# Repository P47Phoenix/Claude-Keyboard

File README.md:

# Claude Keyboard

A 25-key macropad companion for Claude Code terminal sessions — the **Claude Code Pad**. Dedicated hardware for firing CLI shortcuts (accept, reject, allow, arrow keys, commit/PR macros, plan/model cycle) with per-key RGB, a rotary encoder, a 2U stabilized Enter, and RFID artisan keycap support.

Wireless multi-host via BLE on a Seeed XIAO nRF52840; firmware runs [ZMK](https://zmk.dev).

## Status

**Design-complete (2026-04-23).** Gerbers + case STLs + firmware UF2 are produced, reviewed, and committed. Hardware bring-up + bench verification of the safety thresholds is the next physical step.

| Phase | Scope | State |
|---|---|---|
| 1 | PCB design (schematic, layout, routing, gerbers, BOM, CPL) | **Closed** (11 cycles) |
| 2 | 3D-printed case + bottom plate (CadQuery, PETG) | **Closed** (3 cycles) |
| 3 | Firmware (ZMK on nRF52840) | **Closed** (3 cycles) — `west build` clean, ztest 10/10 |
| 4 | TinyML callouts | **Retired** (Cycle 1 arbitration) |
| 5 | RFID figurine keycap base | **Retired** (post-Phase-3 scope decision) |
| 6 | Integration review | **Retired** (post-Phase-3 scope decision) |

PN532 NFC header + I²C bus remain on the PCB for any future revisit; firmware can wire them up later without a board respin.

## Hardware highlights

- **MCU:** Seeed XIAO nRF52840 (direct-solder castellations). BLE 5.x multi-host. Retired the initial XIAO ESP32-S3 + TinyML/OLED path in favour of a simpler, better-supported stack.
- **Keyswitches:** 24× 1U + 1× 2U Enter, Kailh MX hot-swap (Keebio `MX_Only_HS`), 19.05 mm pitch, Cherry plate-mount 2U stabilizer (slotted housing holes per community canonical footprint).
- **RGB:** 25× SK6812MINI-E reverse-mount, one per key, serpentine chain. Firmware-capped at 300 mA peak per IEC 62368-1 Annex Q.
- **Encoder:** EC11 with metal shaft grounded through plated mounting lugs; ESD TVS on all three encoder signals.
- **NFC:** PN532 header for RFID artisan figurine personality switching (Phase 5).
- **Power:** 1S LiPo via JST-PH with **mandatory cell-level protection PCB** (approved cells from Adafruit/SparkFun — see `docs/build-guide.md`). On-board DMG3415U-7 P-FET reverse-polarity, 500 mA PTC, SPDT slide switch. Charging via the XIAO's USB-C + on-module charger.
- **Safety:** NTC cell-temperature monitor, 5× ESD9L3.3 TVS on exposed I²C + encoder, firmware LED cap + VBAT undervoltage cutoff (3.70 V LEDs-on / 3.50 V LEDs-off).
- **Board:** 120 × 132 mm, 2-layer FR4, HASL lead-free, black soldermask. Freerouting-autorouted (1095 segments, 148 GND stitching vias, antenna keepout inviolate).

## Repository layout

```
claude-code-pad/
├── pcb/                           # Phase 1 deliverables
│   ├── claude-code-pad.kicad_pro|sch|pcb
│   ├── gerbers/                   # 10 layers + drill + job file (fab-ready)
│   ├── bom.csv / cpl.csv          # JLCPCB format
│   ├── DESIGN-NOTES.md            # design rationale + cycle history + pinout verification
│   └── _gen/                      # generator + autoroute pipeline
│       ├── generate.py            # schematic + placement source of truth
│       └── autoroute/             # export_dsn + freerouting + import_ses + widen_power + stitch_gnd
├── firmware/
│   ├── zmk/                       # Phase 3 primary (nRF52840 + ZMK)
│   │   └── README.md              # Hard Requirements for FW-1
│   └── qmk/                       # alternate path (RP2040)
├── case/                          # Phase 2 (MECH-1, CadQuery)
├── figurines/                     # Phase 5 (RFID artisan keycap)
└── docs/
    ├── build-guide.md             # MANDATORY battery requirements + assembly
    └── review-log.md              # Adversarial review paper trail
```

## Orchestration

Design work is done by **persona sub-agents** dispatched via Claude's Agent tool, not by the main thread:

- **Designers** (ECE-1 for PCB, MECH-1 for case, FW-1 for firmware) produce deliverables.
- **Adversarial reviewers** (RED-DFM, RED-SAFETY, RED-COST, RED-MECH, RED-FW) critique in parallel.
- Primary designer iterates until BLOCKER/MAJOR findings clear.
- Every cycle is logged in `claude-code-pad/docs/review-log.md`.

Full orchestration spec: `/var/home/meconnelly/Downloads/claude-code-pad-orchestrated-prompt.md` (authoritative for personas, phases, and reviewers).

## Tooling

This repo targets a **Bazzite** (immutable Fedora atomic) workstation. Package management notes and KiCad / Freerouting / Distrobox conventions are in [`CLAUDE.md`](./CLAUDE.md).

- **KiCad 10.0.1** as a Flatpak (`org.kicad.KiCad`) for GUI + authoritative file reads.
- **KiCad 9.0.8** in a `kicad` distrobox (Podman-backed Fedora 43 toolbox) for kicad-cli automation + the KiCad MCP server (`lamaalrajih/kicad-mcp`, auto-loaded via `.mcp.json`).
- **Freerouting 2.1.0** (Java 21) in the same distrobox for headless autorouting.
- **CadQuery / OpenSCAD** (Phase 2) — user-space Python, no Bazzite layering needed.

### Quick commands

```bash
# DRC via kicad-cli (flatpak, matches GUI rule set)
flatpak run --command=kicad-cli org.kicad.KiCad pcb drc \
  --output /tmp/drc.rpt pcb/claude-code-pad.kicad_pcb

# Open the PCB in the GUI
flatpak run --command=pcbnew org.kicad.KiCad pcb/claude-code-pad.kicad_pcb

# Re-run Freerouting (from distrobox)
distrobox enter kicad -- python3 pcb/_gen/autoroute/export_dsn.py pcb/claude-code-pad.kicad_pcb
distrobox enter kicad -- java -jar ~/.local/share/freerouting/freerouting.jar \
  -de /tmp/claude-code-pad.dsn -do /tmp/claude-code-pad.ses
distrobox enter kicad -- python3 pcb/_gen/autoroute/import_ses.py pcb/claude-code-pad.kicad_pcb
```

## Getting involved

If you want to build one:

1. Read [`claude-code-pad/docs/build-guide.md`](claude-code-pad/docs/build-guide.md) first — especially the **mandatory battery requirements** section.
2. Order the PCB from JLCPCB using `claude-code-pad/pcb/gerbers/` and `claude-code-pad/pcb/cpl.csv`.
3. Source the cells from the approved vendor list in the build guide. **Do not substitute a raw LiPo** — the board relies on cell-level protection PCM.
4. Wait for Phase 2 (case STL) and Phase 3 (ZMK firmware) before assembling a complete unit.

## License

TBD.

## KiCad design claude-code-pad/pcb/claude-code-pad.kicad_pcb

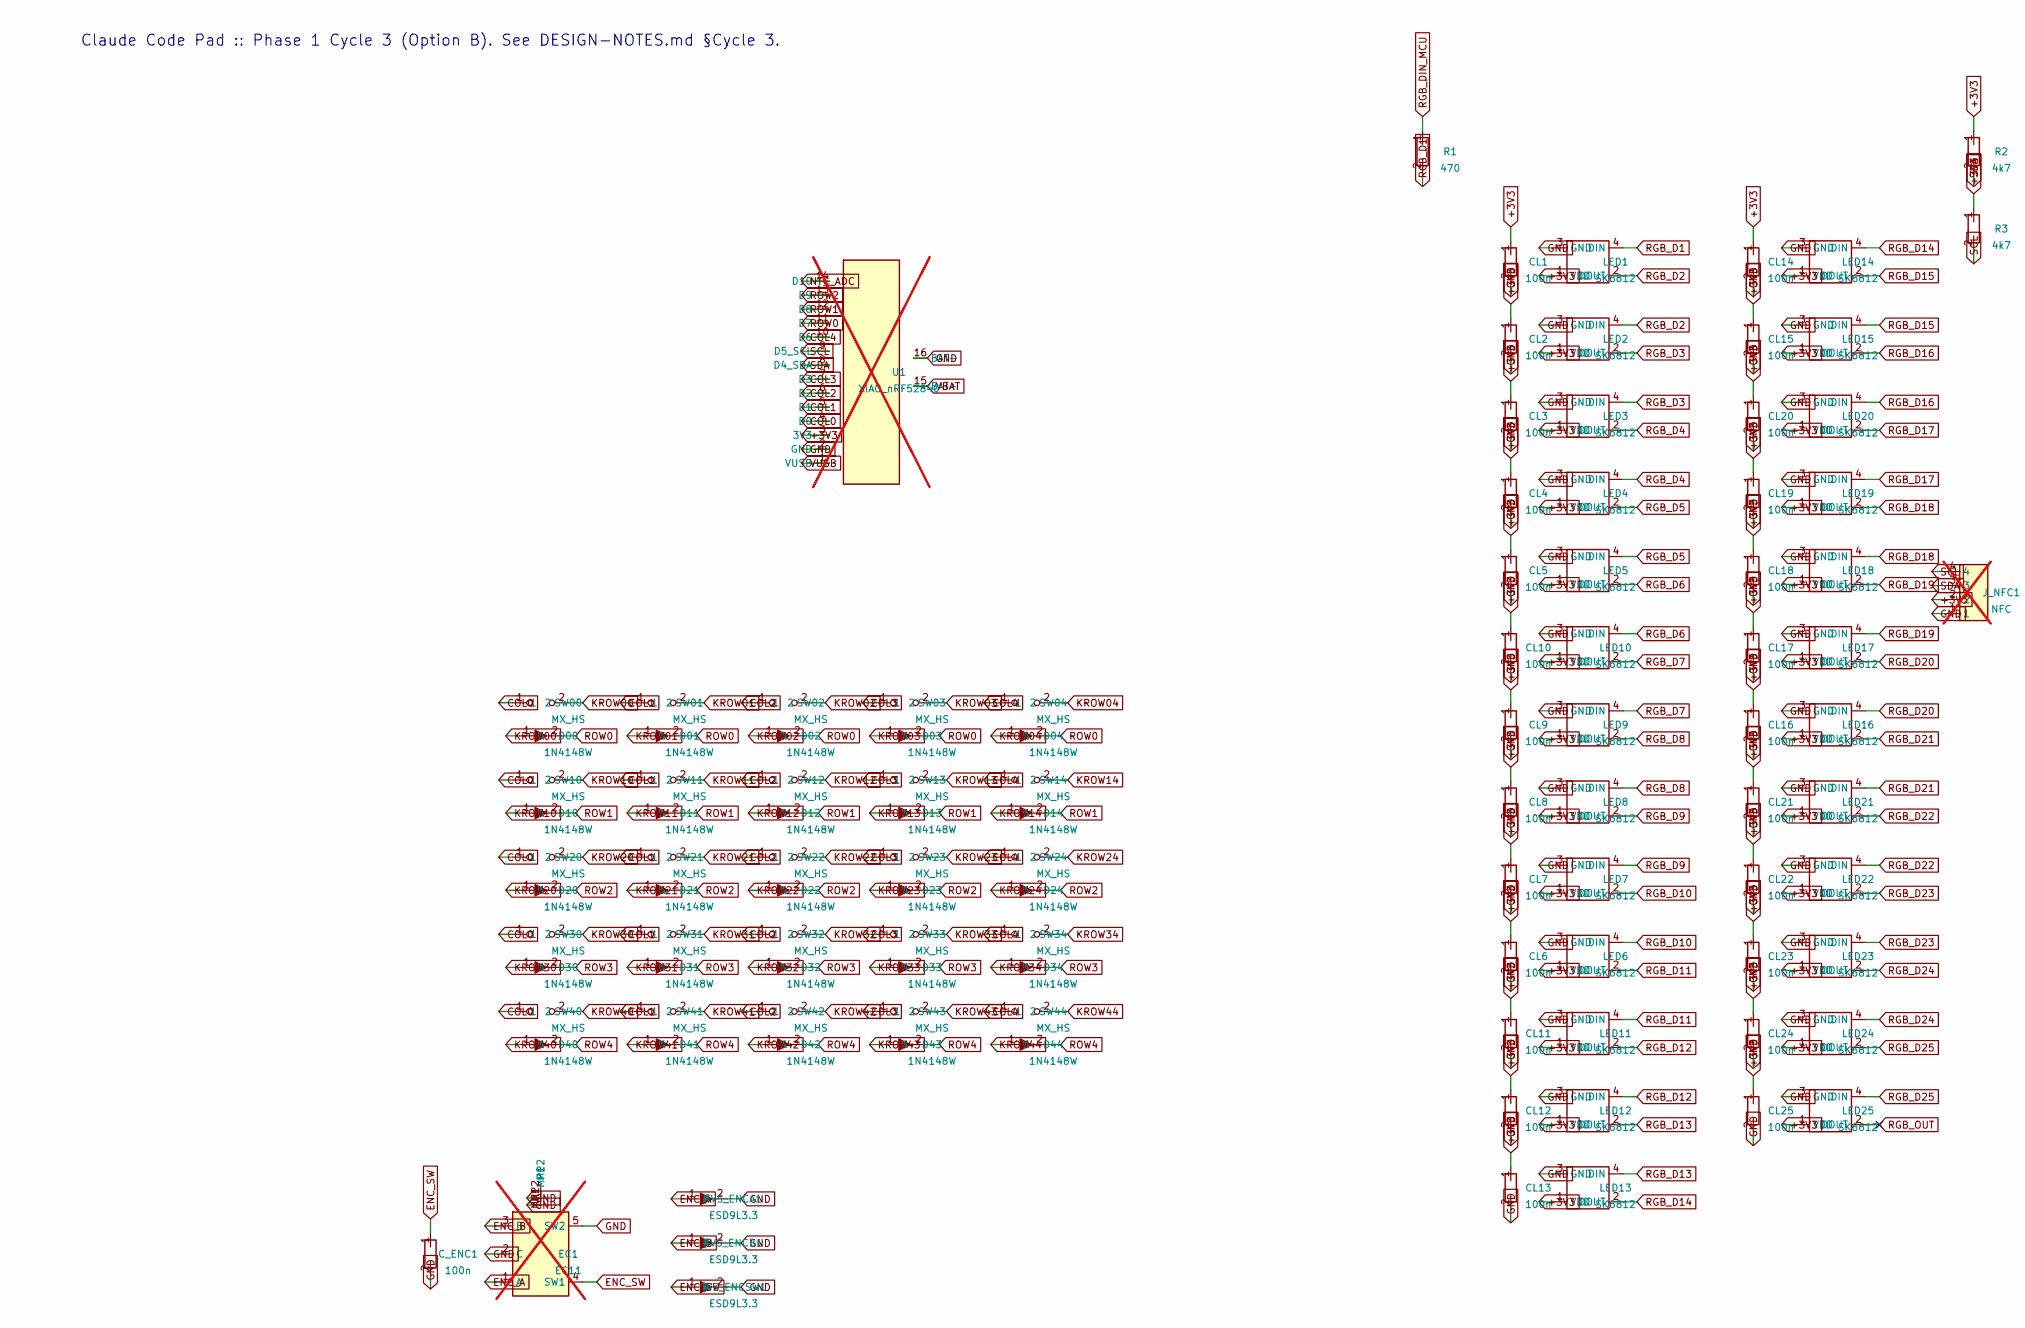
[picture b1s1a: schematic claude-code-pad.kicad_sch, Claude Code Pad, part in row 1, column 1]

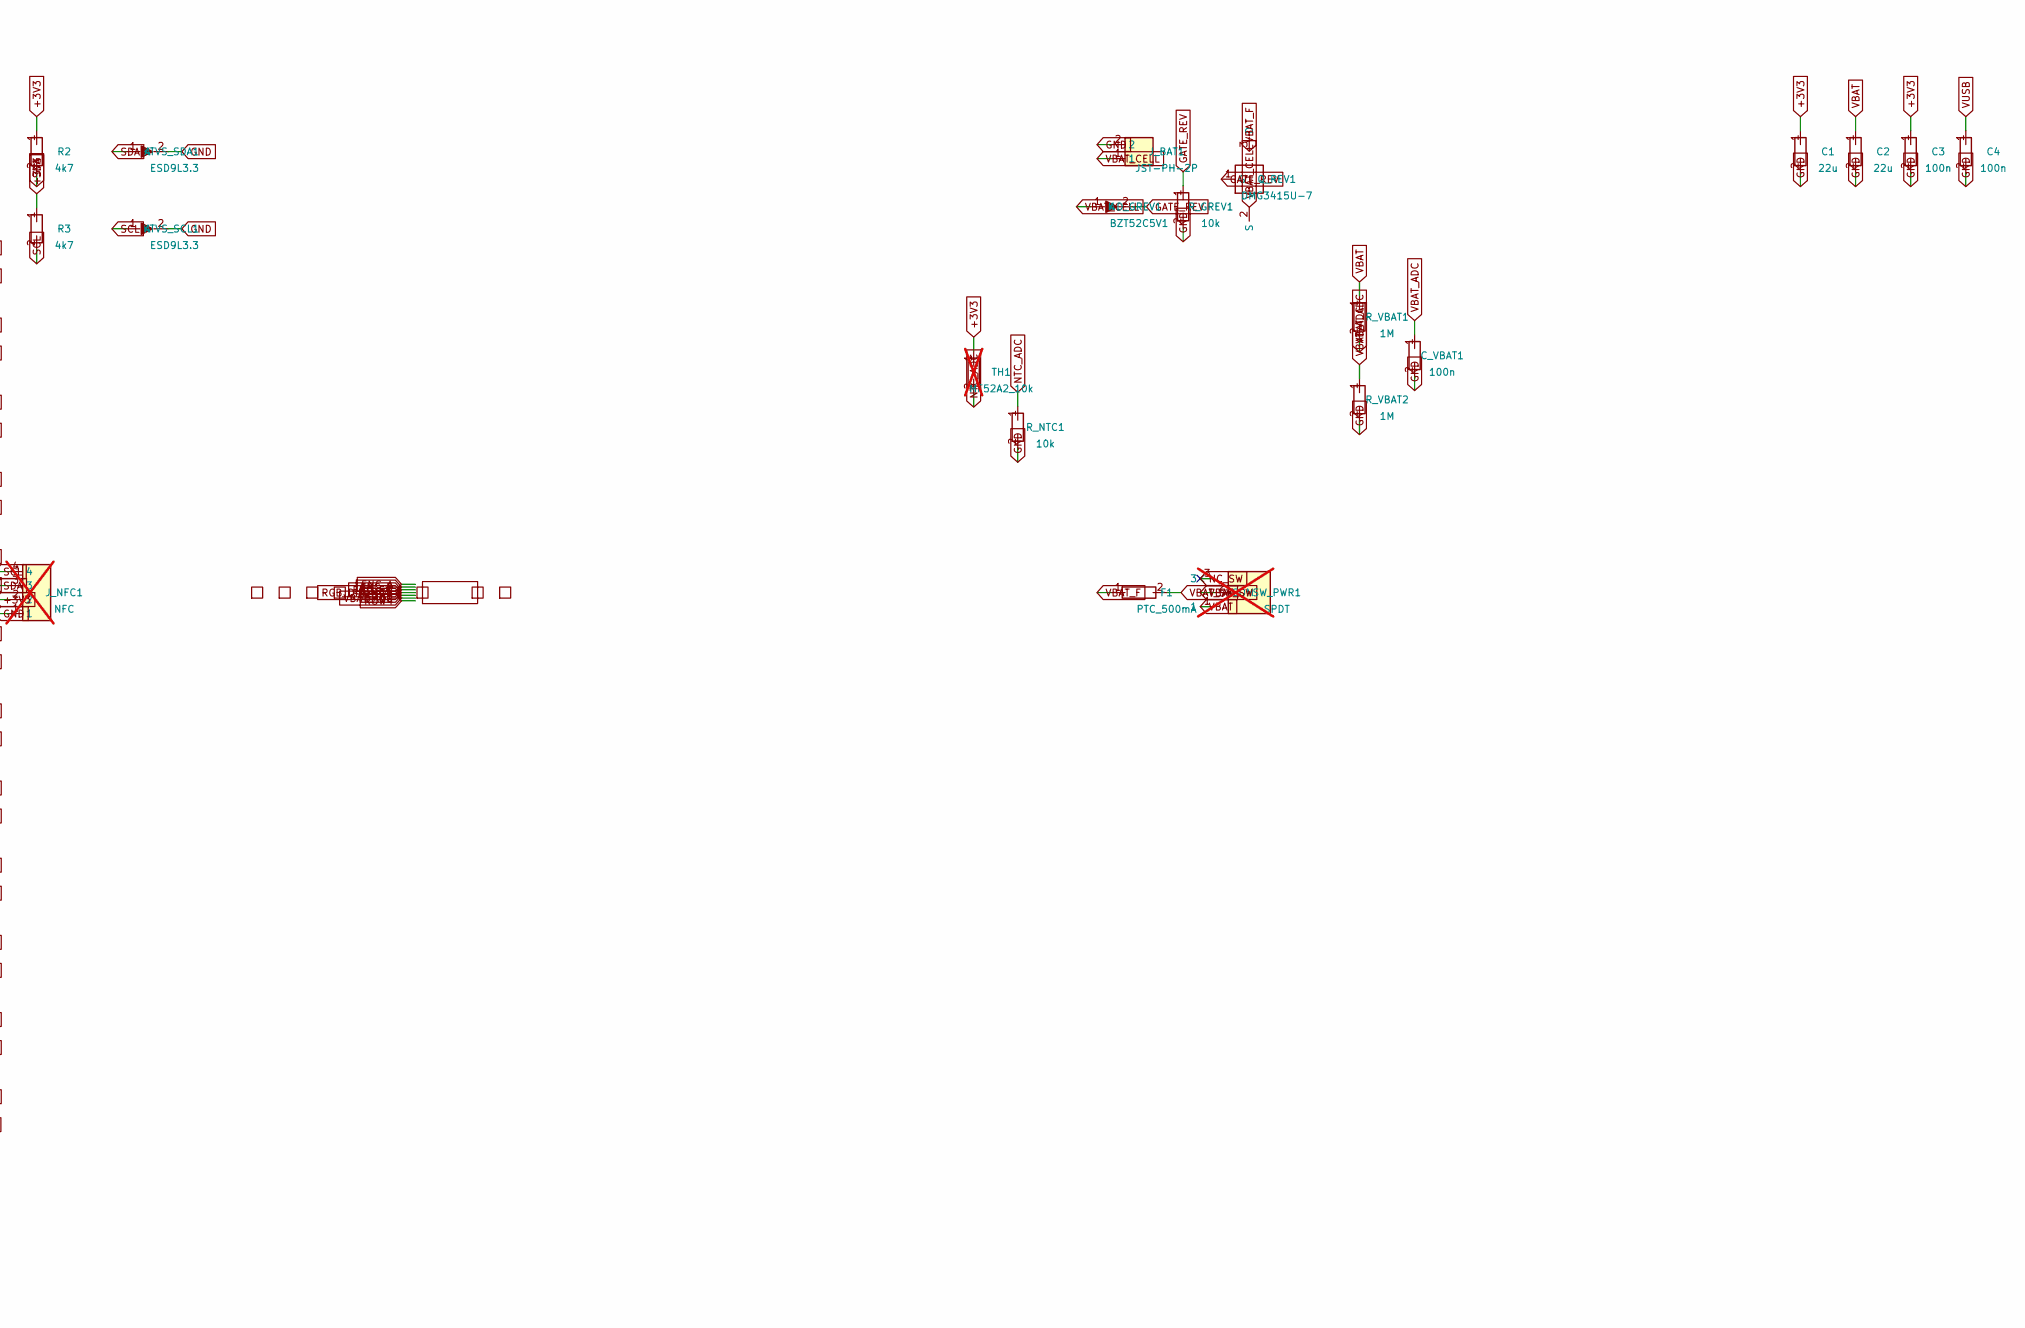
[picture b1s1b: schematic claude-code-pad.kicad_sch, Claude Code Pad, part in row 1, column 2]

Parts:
C1, C2: 22u; C_0805_2012Metric; LCSC C45783
C3, C4: 100n; C_0402_1005Metric; LCSC C1525
CL1, CL2, CL3, CL4, CL5, CL6, CL7, CL8, CL9, CL10, CL11, CL12, CL13, CL14, CL15, CL16, CL17, CL18, CL19, CL20, CL21, CL22, CL23, CL24, CL25: 100n; C_0402_1005Metric; LCSC C1525
C_ENC1: 100n; C_0402_1005Metric; LCSC C1525
C_VBAT1: 100n; C_0402_1005Metric; LCSC C1525
D00, D01, D02, D03, D04, D10, D11, D12, D13, D14, D20, D21, D22, D23, D24, D30, D31, D32, D33, D34, D40, D41, D42, D43, D44: 1N4148W; D_SOD-123; LCSC C81598
D_GREV1: BZT52C5V1; D_SOD-523; LCSC C8056
EC1: EC11; RotaryEncoder_Alps_EC11E-Switch_Vertical_H20mm; LCSC C255515; not fitted
F1: PTC_500mA; Fuse_0805_2012Metric; LCSC C116170
FID1, FID2, FID3: FID; Fiducial_1mm_Mask2mm
H1, H2: M3; MountingHole_3.2mm_M3
H3, H4: M3; MountingHole_3.2mm_M3_NPTH
J_BAT1: JST-PH-2P; JST_PH_S2B-PH-SM4-TB_1x02-1MP_P2.00mm_Horizontal; LCSC C295747
J_NFC1: NFC; PinHeader_1x04_P2.54mm_Vertical; not fitted
J_XIAO_BP: JUMPER; XIAO_BackPad_Jumper_1x7
LED1, LED2, LED3, LED4, LED5, LED6, LED7, LED8, LED9, LED10, LED11, LED12, LED13, LED14, LED15, LED16, LED17, LED18, LED19, LED20, LED21, LED22, LED23, LED24, LED25: SK6812; LED_SK6812_MINI-E_plccn4_3.5x2.8mm; LCSC C5149201
Q_REV1: DMG3415U-7; SOT-23; LCSC C147581
R1: 470; R_0402_1005Metric; LCSC C25744
R2, R3: 4k7; R_0402_1005Metric; LCSC C25905
R_GREV1: 10k; R_0402_1005Metric; LCSC C25804
R_NTC1: 10k; R_0402_1005Metric; LCSC C25804
R_VBAT1, R_VBAT2: 1M; R_0402_1005Metric; LCSC C22935
SW00, SW01, SW02, SW03, SW04, SW10, SW11, SW12, SW13, SW14, SW20, SW21, SW22, SW23, SW24, SW30, SW31, SW32, SW33, SW34, SW40, SW41, SW42, SW43: MX_HS; SW_Kailh_HotSwap_MX; LCSC C5184526
SW44: MX_HS; SW_Kailh_HotSwap_MX_2U; LCSC C5184526
SW_PWR1: SPDT; SW_Slide_1P2T_SS12D00G4; LCSC C8325; not fitted
TH1: MF52A2_10k; R_Axial_DIN0207_L6.3mm_D2.5mm_P7.62mm_Horizontal; LCSC C14128; not fitted
TP1, TP2: TOOL; MountingHole_1.5mm
TVS_ENCA1: ESD9L3.3; D_SOD-523; LCSC C709011
TVS_ENCB1: ESD9L3.3; D_SOD-523; LCSC C709011
TVS_ENCSW1: ESD9L3.3; D_SOD-523; LCSC C709011
TVS_SCL1: ESD9L3.3; D_SOD-523; LCSC C709011
TVS_SDA1: ESD9L3.3; D_SOD-523; LCSC C709011
U1: XIAO_nRF52840; XIAO_nRF52840_Castellated; LCSC C2888140; not fitted

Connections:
+3V3: C1.1, C3.1, CL1.1, CL2.1, CL3.1, CL4.1, CL5.1, CL6.1, CL7.1, CL8.1, CL9.1, CL10.1, CL11.1, CL12.1, CL13.1, CL14.1, CL15.1, CL16.1, CL17.1, CL18.1, CL19.1, CL20.1, CL21.1, CL22.1, CL23.1, CL24.1, CL25.1, J_NFC1.2, LED1.1 (VDD), LED2.1 (VDD), LED3.1 (VDD), LED4.1 (VDD), LED5.1 (VDD), LED6.1 (VDD), LED7.1 (VDD), LED8.1 (VDD), LED9.1 (VDD), LED10.1 (VDD), LED11.1 (VDD), LED12.1 (VDD), LED13.1 (VDD), LED14.1 (VDD), LED15.1 (VDD), LED16.1 (VDD), LED17.1 (VDD), LED18.1 (VDD), LED19.1 (VDD), LED20.1 (VDD), LED21.1 (VDD), LED22.1 (VDD), LED23.1 (VDD), LED24.1 (VDD), LED25.1 (VDD), R2.1, R3.1, TH1.1, U1.3 (3V3)
COL0: SW00.1, SW10.1, SW20.1, SW30.1, SW40.1, U1.4 (D0)
COL1: SW01.1, SW11.1, SW21.1, SW31.1, SW41.1, U1.5 (D1)
COL2: SW02.1, SW12.1, SW22.1, SW32.1, SW42.1, U1.6 (D2)
COL3: SW03.1, SW13.1, SW23.1, SW33.1, SW43.1, U1.7 (D3)
COL4: SW04.1, SW14.1, SW24.1, SW34.1, SW44.1, U1.10 (D6)
ENC_A: EC1.1 (A), J_XIAO_BP.1, TVS_ENCA1.1 (K)
ENC_B: EC1.3 (B), J_XIAO_BP.2, TVS_ENCB1.1 (K)
ENC_SW: C_ENC1.1, EC1.4 (SW1), J_XIAO_BP.3, TVS_ENCSW1.1 (K)
GATE_REV: D_GREV1.2 (A), Q_REV1.1 (G), R_GREV1.1
GND: C1.2, C2.2, C3.2, C4.2, CL1.2, CL2.2, CL3.2, CL4.2, CL5.2, CL6.2, CL7.2, CL8.2, CL9.2, CL10.2, CL11.2, CL12.2, CL13.2, CL14.2, CL15.2, CL16.2, CL17.2, CL18.2, CL19.2, CL20.2, CL21.2, CL22.2, CL23.2, CL24.2, CL25.2, C_ENC1.2, C_VBAT1.2, EC1.2 (C), EC1.5 (SW2), EC1.MP1, EC1.MP2, FID1.1, FID2.1, FID3.1, H1.1, H2.1, J_BAT1.2, J_NFC1.1, LED1.3 (GND), LED2.3 (GND), LED3.3 (GND), LED4.3 (GND), LED5.3 (GND), LED6.3 (GND), LED7.3 (GND), LED8.3 (GND), LED9.3 (GND), LED10.3 (GND), LED11.3 (GND), LED12.3 (GND), LED13.3 (GND), LED14.3 (GND), LED15.3 (GND), LED16.3 (GND), LED17.3 (GND), LED18.3 (GND), LED19.3 (GND), LED20.3 (GND), LED21.3 (GND), LED22.3 (GND), LED23.3 (GND), LED24.3 (GND), LED25.3 (GND), R_GREV1.2, R_NTC1.2, R_VBAT2.2, TVS_ENCA1.2 (A), TVS_ENCB1.2 (A), TVS_ENCSW1.2 (A), TVS_SCL1.2 (A), TVS_SDA1.2 (A), U1.2 (GND), U1.16 (BAT-)
KROW00: D00.1 (K), SW00.2
KROW01: D01.1 (K), SW01.2
KROW02: D02.1 (K), SW02.2
KROW03: D03.1 (K), SW03.2
KROW04: D04.1 (K), SW04.2
KROW10: D10.1 (K), SW10.2
KROW11: D11.1 (K), SW11.2
KROW12: D12.1 (K), SW12.2
KROW13: D13.1 (K), SW13.2
KROW14: D14.1 (K), SW14.2
KROW20: D20.1 (K), SW20.2
KROW21: D21.1 (K), SW21.2
KROW22: D22.1 (K), SW22.2
KROW23: D23.1 (K), SW23.2
KROW24: D24.1 (K), SW24.2
KROW30: D30.1 (K), SW30.2
KROW31: D31.1 (K), SW31.2
KROW32: D32.1 (K), SW32.2
KROW33: D33.1 (K), SW33.2
KROW34: D34.1 (K), SW34.2
KROW40: D40.1 (K), SW40.2
KROW41: D41.1 (K), SW41.2
KROW42: D42.1 (K), SW42.2
KROW43: D43.1 (K), SW43.2
KROW44: D44.1 (K), SW44.2
NC_SW: SW_PWR1.3
NTC_ADC: R_NTC1.1, TH1.2, U1.14 (D10)
RGB_D1: LED1.4 (DIN), R1.2
RGB_D2: LED1.2 (DOUT), LED2.4 (DIN)
RGB_D3: LED2.2 (DOUT), LED3.4 (DIN)
RGB_D4: LED3.2 (DOUT), LED4.4 (DIN)
RGB_D5: LED4.2 (DOUT), LED5.4 (DIN)
RGB_D6: LED5.2 (DOUT), LED10.4 (DIN)
RGB_D7: LED9.4 (DIN), LED10.2 (DOUT)
RGB_D8: LED8.4 (DIN), LED9.2 (DOUT)
RGB_D9: LED7.4 (DIN), LED8.2 (DOUT)
RGB_D10: LED6.4 (DIN), LED7.2 (DOUT)
RGB_D11: LED6.2 (DOUT), LED11.4 (DIN)
RGB_D12: LED11.2 (DOUT), LED12.4 (DIN)
RGB_D13: LED12.2 (DOUT), LED13.4 (DIN)
RGB_D14: LED13.2 (DOUT), LED14.4 (DIN)
RGB_D15: LED14.2 (DOUT), LED15.4 (DIN)
RGB_D16: LED15.2 (DOUT), LED20.4 (DIN)
RGB_D17: LED19.4 (DIN), LED20.2 (DOUT)
RGB_D18: LED18.4 (DIN), LED19.2 (DOUT)
RGB_D19: LED17.4 (DIN), LED18.2 (DOUT)
RGB_D20: LED16.4 (DIN), LED17.2 (DOUT)
RGB_D21: LED16.2 (DOUT), LED21.4 (DIN)
RGB_D22: LED21.2 (DOUT), LED22.4 (DIN)
RGB_D23: LED22.2 (DOUT), LED23.4 (DIN)
RGB_D24: LED23.2 (DOUT), LED24.4 (DIN)
RGB_D25: LED24.2 (DOUT), LED25.4 (DIN)
RGB_DIN_MCU: J_XIAO_BP.4, R1.1
RGB_OUT: LED25.2 (DOUT)
ROW0: D00.2 (A), D01.2 (A), D02.2 (A), D03.2 (A), D04.2 (A), U1.11 (D7)
ROW1: D10.2 (A), D11.2 (A), D12.2 (A), D13.2 (A), D14.2 (A), U1.12 (D8)
ROW2: D20.2 (A), D21.2 (A), D22.2 (A), D23.2 (A), D24.2 (A), U1.13 (D9)
ROW3: D30.2 (A), D31.2 (A), D32.2 (A), D33.2 (A), D34.2 (A), J_XIAO_BP.5
ROW4: D40.2 (A), D41.2 (A), D42.2 (A), D43.2 (A), D44.2 (A), J_XIAO_BP.7
SCL: J_NFC1.4, R3.2, TVS_SCL1.1 (K), U1.9 (D5_SCL)
SDA: J_NFC1.3, R2.2, TVS_SDA1.1 (K), U1.8 (D4_SDA)
VBAT: C2.1, R_VBAT1.1, SW_PWR1.1, U1.15 (BAT+)
VBAT_ADC: C_VBAT1.1, J_XIAO_BP.6, R_VBAT1.2, R_VBAT2.1
VBAT_CELL: D_GREV1.1 (K), J_BAT1.1, Q_REV1.2 (S)
VBAT_F: F1.1, Q_REV1.3 (D)
VBAT_SW: F1.2, SW_PWR1.2 (COM)
VUSB: C4.1, U1.1 (VUSB)

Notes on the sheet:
Claude Code Pad :: Phase 1 Cycle 3 (Option B). See DESIGN-NOTES.md §Cycle 3.

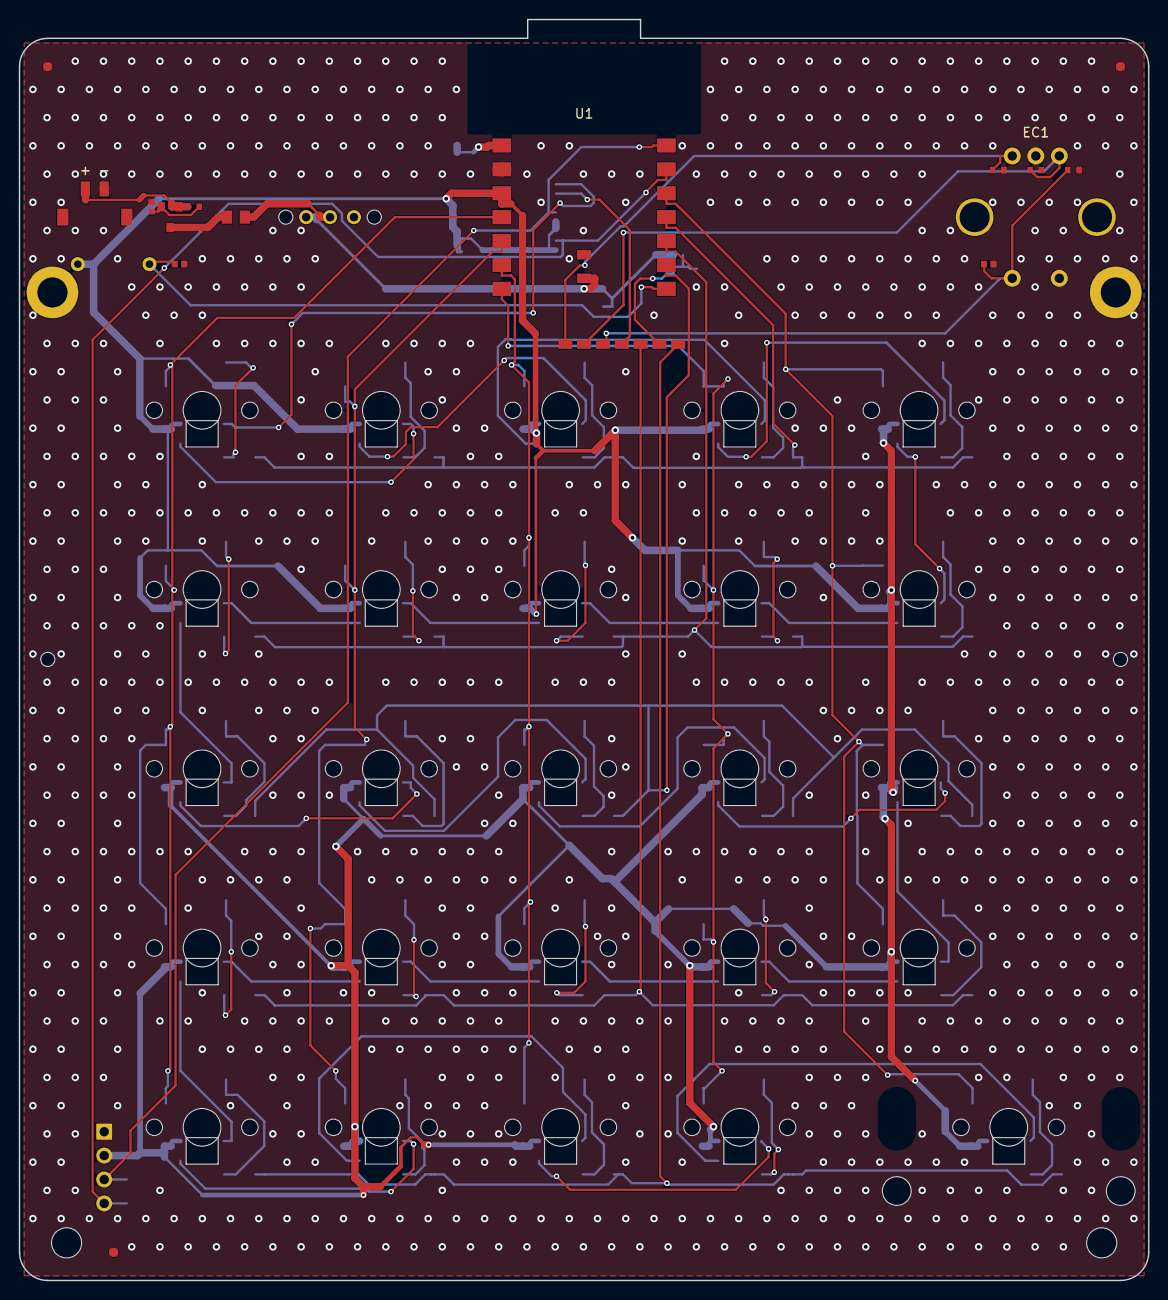
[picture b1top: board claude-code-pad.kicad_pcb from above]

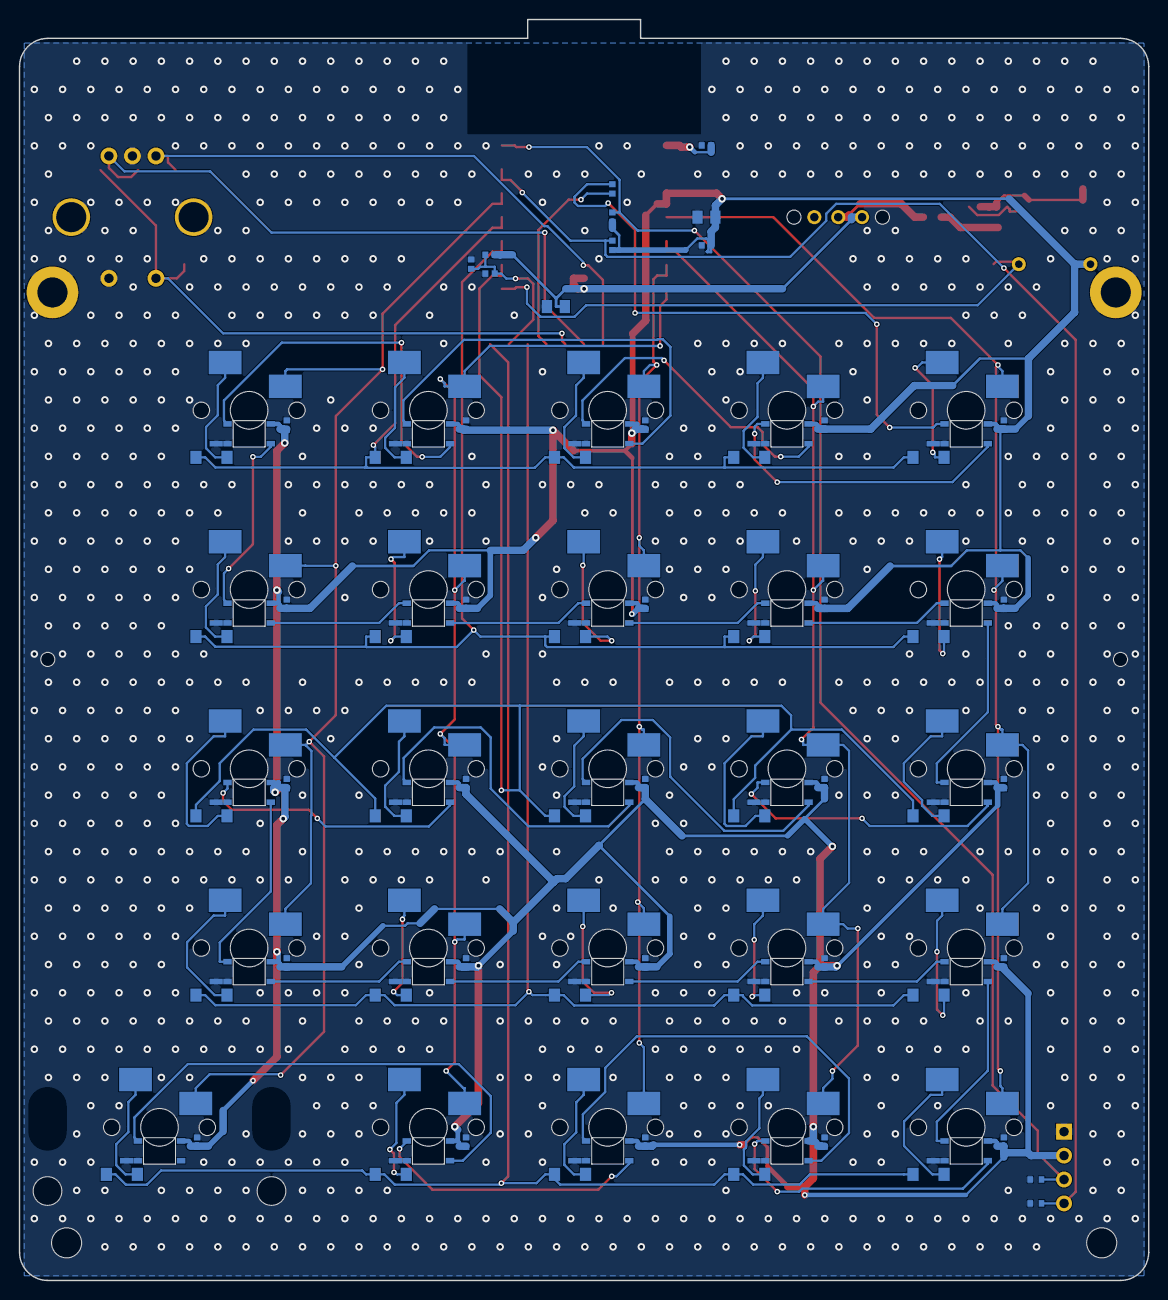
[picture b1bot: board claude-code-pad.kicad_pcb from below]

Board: 2 copper layers, 120.0 x 134.0 mm, 137 parts (87 on the bottom side), 76 nets.

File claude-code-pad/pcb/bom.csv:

"Refs","Value","Footprint","Qty","DNP"
"C1","22u","claude-code-pad:C_0805_2012Metric","1",""
"C2","22u","claude-code-pad:C_0805_2012Metric","1",""
"C3","100n","claude-code-pad:C_0402_1005Metric","1",""
"C4","100n","claude-code-pad:C_0402_1005Metric","1",""
"CL1","100n","claude-code-pad:C_0402_1005Metric","1",""
"CL2","100n","claude-code-pad:C_0402_1005Metric","1",""
"CL3","100n","claude-code-pad:C_0402_1005Metric","1",""
"CL4","100n","claude-code-pad:C_0402_1005Metric","1",""
"CL5","100n","claude-code-pad:C_0402_1005Metric","1",""
"CL6","100n","claude-code-pad:C_0402_1005Metric","1",""
"CL7","100n","claude-code-pad:C_0402_1005Metric","1",""
"CL8","100n","claude-code-pad:C_0402_1005Metric","1",""
"CL9","100n","claude-code-pad:C_0402_1005Metric","1",""
"CL10","100n","claude-code-pad:C_0402_1005Metric","1",""
"CL11","100n","claude-code-pad:C_0402_1005Metric","1",""
"CL12","100n","claude-code-pad:C_0402_1005Metric","1",""
"CL13","100n","claude-code-pad:C_0402_1005Metric","1",""
"CL14","100n","claude-code-pad:C_0402_1005Metric","1",""
"CL15","100n","claude-code-pad:C_0402_1005Metric","1",""
"CL16","100n","claude-code-pad:C_0402_1005Metric","1",""
"CL17","100n","claude-code-pad:C_0402_1005Metric","1",""
"CL18","100n","claude-code-pad:C_0402_1005Metric","1",""
"CL19","100n","claude-code-pad:C_0402_1005Metric","1",""
"CL20","100n","claude-code-pad:C_0402_1005Metric","1",""
"CL21","100n","claude-code-pad:C_0402_1005Metric","1",""
"CL22","100n","claude-code-pad:C_0402_1005Metric","1",""
"CL23","100n","claude-code-pad:C_0402_1005Metric","1",""
"CL24","100n","claude-code-pad:C_0402_1005Metric","1",""
"CL25","100n","claude-code-pad:C_0402_1005Metric","1",""
"C_ENC1","100n","claude-code-pad:C_0402_1005Metric","1",""
"C_VBAT1","100n","claude-code-pad:C_0402_1005Metric","1",""
"D00","1N4148W","claude-code-pad:D_SOD-123","1",""
"D01","1N4148W","claude-code-pad:D_SOD-123","1",""
"D02","1N4148W","claude-code-pad:D_SOD-123","1",""
"D03","1N4148W","claude-code-pad:D_SOD-123","1",""
"D04","1N4148W","claude-code-pad:D_SOD-123","1",""
"D10","1N4148W","claude-code-pad:D_SOD-123","1",""
"D11","1N4148W","claude-code-pad:D_SOD-123","1",""
"D12","1N4148W","claude-code-pad:D_SOD-123","1",""
"D13","1N4148W","claude-code-pad:D_SOD-123","1",""
"D14","1N4148W","claude-code-pad:D_SOD-123","1",""
"D20","1N4148W","claude-code-pad:D_SOD-123","1",""
"D21","1N4148W","claude-code-pad:D_SOD-123","1",""
"D22","1N4148W","claude-code-pad:D_SOD-123","1",""
"D23","1N4148W","claude-code-pad:D_SOD-123","1",""
"D24","1N4148W","claude-code-pad:D_SOD-123","1",""
"D30","1N4148W","claude-code-pad:D_SOD-123","1",""
"D31","1N4148W","claude-code-pad:D_SOD-123","1",""
"D32","1N4148W","claude-code-pad:D_SOD-123","1",""
"D33","1N4148W","claude-code-pad:D_SOD-123","1",""
"D34","1N4148W","claude-code-pad:D_SOD-123","1",""
"D40","1N4148W","claude-code-pad:D_SOD-123","1",""
"D41","1N4148W","claude-code-pad:D_SOD-123","1",""
"D42","1N4148W","claude-code-pad:D_SOD-123","1",""
"D43","1N4148W","claude-code-pad:D_SOD-123","1",""
"D44","1N4148W","claude-code-pad:D_SOD-123","1",""
"D_GREV1","BZT52C5V1","claude-code-pad:D_SOD-523","1",""
"F1","PTC_500mA","claude-code-pad:Fuse_0805_2012Metric","1",""
"J_BAT1","JST-PH-2P","claude-code-pad:JST_PH_S2B-PH-SM4-TB_1x02-1MP_P2.00mm_Horizontal","1",""
"LED1","SK6812","claude-code-pad:LED_SK6812_MINI-E_plccn4_3.5x2.8mm","1",""
"LED2","SK6812","claude-code-pad:LED_SK6812_MINI-E_plccn4_3.5x2.8mm","1",""
"LED3","SK6812","claude-code-pad:LED_SK6812_MINI-E_plccn4_3.5x2.8mm","1",""
"LED4","SK6812","claude-code-pad:LED_SK6812_MINI-E_plccn4_3.5x2.8mm","1",""
"LED5","SK6812","claude-code-pad:LED_SK6812_MINI-E_plccn4_3.5x2.8mm","1",""
"LED6","SK6812","claude-code-pad:LED_SK6812_MINI-E_plccn4_3.5x2.8mm","1",""
"LED7","SK6812","claude-code-pad:LED_SK6812_MINI-E_plccn4_3.5x2.8mm","1",""
"LED8","SK6812","claude-code-pad:LED_SK6812_MINI-E_plccn4_3.5x2.8mm","1",""
"LED9","SK6812","claude-code-pad:LED_SK6812_MINI-E_plccn4_3.5x2.8mm","1",""
"LED10","SK6812","claude-code-pad:LED_SK6812_MINI-E_plccn4_3.5x2.8mm","1",""
"LED11","SK6812","claude-code-pad:LED_SK6812_MINI-E_plccn4_3.5x2.8mm","1",""
"LED12","SK6812","claude-code-pad:LED_SK6812_MINI-E_plccn4_3.5x2.8mm","1",""
"LED13","SK6812","claude-code-pad:LED_SK6812_MINI-E_plccn4_3.5x2.8mm","1",""
"LED14","SK6812","claude-code-pad:LED_SK6812_MINI-E_plccn4_3.5x2.8mm","1",""
"LED15","SK6812","claude-code-pad:LED_SK6812_MINI-E_plccn4_3.5x2.8mm","1",""
"LED16","SK6812","claude-code-pad:LED_SK6812_MINI-E_plccn4_3.5x2.8mm","1",""
"LED17","SK6812","claude-code-pad:LED_SK6812_MINI-E_plccn4_3.5x2.8mm","1",""
"LED18","SK6812","claude-code-pad:LED_SK6812_MINI-E_plccn4_3.5x2.8mm","1",""
"LED19","SK6812","claude-code-pad:LED_SK6812_MINI-E_plccn4_3.5x2.8mm","1",""
"LED20","SK6812","claude-code-pad:LED_SK6812_MINI-E_plccn4_3.5x2.8mm","1",""
"LED21","SK6812","claude-code-pad:LED_SK6812_MINI-E_plccn4_3.5x2.8mm","1",""
"LED22","SK6812","claude-code-pad:LED_SK6812_MINI-E_plccn4_3.5x2.8mm","1",""
"LED23","SK6812","claude-code-pad:LED_SK6812_MINI-E_plccn4_3.5x2.8mm","1",""
"LED24","SK6812","claude-code-pad:LED_SK6812_MINI-E_plccn4_3.5x2.8mm","1",""
"LED25","SK6812","claude-code-pad:LED_SK6812_MINI-E_plccn4_3.5x2.8mm","1",""
"Q_REV1","DMG3415U-7","claude-code-pad:SOT-23","1",""
"R1","470","claude-code-pad:R_0402_1005Metric","1",""
"R2","4k7","claude-code-pad:R_0402_1005Metric","1",""
"R3","4k7","claude-code-pad:R_0402_1005Metric","1",""
"R_GREV1","10k","claude-code-pad:R_0402_1005Metric","1",""
"R_NTC1","10k","claude-code-pad:R_0402_1005Metric","1",""
"R_VBAT1","1M","claude-code-pad:R_0402_1005Metric","1",""
"R_VBAT2","1M","claude-code-pad:R_0402_1005Metric","1",""
"SW00","MX_HS","claude-code-pad:SW_Kailh_HotSwap_MX","1",""
"SW01","MX_HS","claude-code-pad:SW_Kailh_HotSwap_MX","1",""
"SW02","MX_HS","claude-code-pad:SW_Kailh_HotSwap_MX","1",""
"SW03","MX_HS","claude-code-pad:SW_Kailh_HotSwap_MX","1",""
"SW04","MX_HS","claude-code-pad:SW_Kailh_HotSwap_MX","1",""
"SW10","MX_HS","claude-code-pad:SW_Kailh_HotSwap_MX","1",""
"SW11","MX_HS","claude-code-pad:SW_Kailh_HotSwap_MX","1",""
"SW12","MX_HS","claude-code-pad:SW_Kailh_HotSwap_MX","1",""
"SW13","MX_HS","claude-code-pad:SW_Kailh_HotSwap_MX","1",""
"SW14","MX_HS","claude-code-pad:SW_Kailh_HotSwap_MX","1",""
"SW20","MX_HS","claude-code-pad:SW_Kailh_HotSwap_MX","1",""
"SW21","MX_HS","claude-code-pad:SW_Kailh_HotSwap_MX","1",""
"SW22","MX_HS","claude-code-pad:SW_Kailh_HotSwap_MX","1",""
"SW23","MX_HS","claude-code-pad:SW_Kailh_HotSwap_MX","1",""
"SW24","MX_HS","claude-code-pad:SW_Kailh_HotSwap_MX","1",""
"SW30","MX_HS","claude-code-pad:SW_Kailh_HotSwap_MX","1",""
"SW31","MX_HS","claude-code-pad:SW_Kailh_HotSwap_MX","1",""
"SW32","MX_HS","claude-code-pad:SW_Kailh_HotSwap_MX","1",""
"SW33","MX_HS","claude-code-pad:SW_Kailh_HotSwap_MX","1",""
"SW34","MX_HS","claude-code-pad:SW_Kailh_HotSwap_MX","1",""
"SW40","MX_HS","claude-code-pad:SW_Kailh_HotSwap_MX","1",""
"SW41","MX_HS","claude-code-pad:SW_Kailh_HotSwap_MX","1",""
"SW42","MX_HS","claude-code-pad:SW_Kailh_HotSwap_MX","1",""
"SW43","MX_HS","claude-code-pad:SW_Kailh_HotSwap_MX","1",""
"SW44","MX_HS","claude-code-pad:SW_Kailh_HotSwap_MX_2U","1",""
"TVS_ENCA1","ESD9L3.3","claude-code-pad:D_SOD-523","1",""
"TVS_ENCB1","ESD9L3.3","claude-code-pad:D_SOD-523","1",""
"TVS_ENCSW1","ESD9L3.3","claude-code-pad:D_SOD-523","1",""
"TVS_SCL1","ESD9L3.3","claude-code-pad:D_SOD-523","1",""
"TVS_SDA1","ESD9L3.3","claude-code-pad:D_SOD-523","1",""

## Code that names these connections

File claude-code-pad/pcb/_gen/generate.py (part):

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    the MCU body, never touching the MCU front castellation F.Cu pads.

  * C5-B3 (Q_REV gate shorted to source): R_GREV moved adjacent to
    Q_REV pin 1 (centred 2 mm east of gate pad). GATE_REV copper under
    3 mm total length before reaching R_GREV pin 1 and D_GREV anode.
    Routed F.Cu only, no via, no detour -- no VBAT_CELL crossing.

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        documented in DESIGN-NOTES §Safety and firmware/zmk/README.md.
        Fixes B-PCM-REG.
      - Back-pad jumper cluster eliminated: NTC_ADC promoted to front
        castellation pin (D10 was ROW3 -> moves to encoder A; the full
        pin map reshuffle is in §Pin map). Only ROW4/ENC_A/ENC_B/ENC_SW/
        RGB_DIN remain on rear pads and the cluster is placed 4 mm
        south of the MCU body (not 120 mm away). Fixes B-RATNEST-PWR.
      - J_BAT (JST) -> Q_REV -> F1 -> SW_PWR -> VBAT -> XIAO BAT+
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    # Cycle 9 B1 fix: KiCad library-symbol Y is up-positive but the
    # schematic Y is down-positive. Cycles 1-8 used lib-up Y (+5.08 for
    # pin 1) while the wire/global-label emitter used sheet-down Y for
    # the same position -- so ENC_A ended up electrically on pin 3 (B)
    # and ENC_B on pin 1 (A); pins 4/5 likewise swapped (ENC_SW to the
    # GND lug, GND to the switch pin). The PCB was correct; the
    # schematic was the offender. Y signs here are now
    # correct-for-sheet-coordinates, and MP1/MP2 are the two mounting
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    ))
    # Cycle 3 pin-map (14 front pins + 2 rear BAT pads). Post Option B the
    # +3V3_SYS net is gone; XIAO's 3V3 pin drives the whole +3V3 rail.
    # NTC_ADC moved to D10 (front pin) -- was rear pad in Cycle 2.
    xiao_map = [
        (1,  "VUSB"),      # 5V USB rail (USB-C on module)
        (2,  "GND"),
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    # Q_REV DMG3415U-7 P-FET reverse-polarity protection.
    # Datasheet: Diodes DS31735 Rev. 14 -- SOT-23 pin1=Gate, pin2=Source, pin3=Drain.
    # Conduction:
    #   cell+ connected to Source (pin 2). Drain (pin 3) -> downstream VBAT_F (pre-fuse).
    #   Gate (pin 1) pulled to GND via R_GREV 10k. Vgs = -Vbat = -3.7 V when cell
    #   installed correctly -> FET ON (Vgs(th) = -0.9 V typ, Rds(on) ~ 0.08 Ω
    #   at Vgs=-2.5V so ~0.12 Ω at Vgs=-3.7V -- fine for 300 mA load).
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    # symbol pin 1 -> VBAT (ON throw)
    out.append(wire(520 - 6.35, 120 + 2.54, 520 - 8.89, 120 + 2.54, "swpwr1"))
    out.append(gl("VBAT", 520 - 8.89, 120 + 2.54, 180))
    # symbol pin 2 (COM) -> VBAT_SW (post-fuse)
    out.append(wire(520 - 6.35, 120, 520 - 8.89, 120, "swpwr2"))
    out.append(gl("VBAT_SW", 520 - 8.89, 120, 180))
    # symbol pin 3 (OFF throw) -> NC_SW (floating)
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    hallucinated; the smaller 1.0 mm pitch JST connector family is not
    the common ecosystem for protected 1S cells).

    Pin 1 (+VBAT_CELL) is WEST of centre; pin 2 (GND) is EAST. F.SilkS
    glyphs \"+\" and \"-\" sit immediately north of each pad (C5-M3 fix
    for S-C4-M1: builders must see the polarity marker).
    LCSC C295747 (S2B-PH-SM4-TB), 2.0 mm pitch, side-entry SMD."""
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                                mcu_pin_nets_front, mcu_pin_nets_bat))

    # Rear-pad jumper cluster. Cycle 4: slot assignment re-ordered so
    # ROW3/ROW4 are not aligned with COL F.Cu spine x-coordinates
    # (115.55 / 134.6 / 153.65 / 172.7 / 191.75). Slot x positions:
    #   slot 0 = mcu_x - 6 = 151.5
    #   slot 1 = mcu_x - 4 = 153.5  (was ROW4 -- 0.15 mm from COL2 spine)
    #   slot 2 = mcu_x - 2 = 155.5
    #   slot 3 = mcu_x + 0 = 157.5
    #   slot 4 = mcu_x + 2 = 159.5
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
    # --- PN532 NFC header ----------------------------------------------------
    # Cycle 4: moved north-east to (x0+13, y1-15) so header body sits in
    # the band south of ROW4 spine (y=224.725) and well west of the ROW
    # lane vias at x=x1-18..x1-26. Vertical orientation (rotation 90 keeps
    # pins in y-column).
    nfc_hdr_x = x0 + 9
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    out.append(fp_sot23_3(
        "Q_REV1", "DMG3415U-7",
        qrev_x, qrev_y, 0, {
            1: (idx["GATE_REV"], "GATE_REV"),     # Pin 1 = Gate
            2: (idx["VBAT_CELL"], "VBAT_CELL"),    # Pin 2 = Source (cell+)
            3: (idx["VBAT_F"], "VBAT_F"),          # Pin 3 = Drain (to fuse)
        }, rotation_hint="180",
    ))
    # R_GREV 10k (gate -> GND). Cycle 5 (C5-B3): place DIRECTLY adjacent
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    #   pad 2 NORTH at (qrev_x-1.95, qrev_y-1.6) = GND (pour)
    # R_GREV body (0402, 0.5 mm body_h rot 90 becomes ±0.25 in x) occupies
    # x = qrev_x-2.2 .. qrev_x-1.7; clear of Q_REV body (qrev_x +/- 0.65).
    # Short GATE_REV F.Cu track: Q_REV pin 1 east edge of pad at
    # (qrev_x-0.55, qrev_y-1.1) -> R_GREV pad 1 (south pad) east edge at
    # (qrev_x-1.65, qrev_y-0.6). Trace run: from Q_REV pin 1 south-east
    # corner at (qrev_x-0.95, qrev_y-0.6) west to (qrev_x-1.65, qrev_y-0.6)
    # = 0.7 mm on F.Cu. Total GATE_REV copper < 2.5 mm (pin 1 body
    # + stub + pad).
    out.append(fp_0402("R_GREV1", "10k", qrev_x - 1.95, qrev_y - 1.1, 90,
                       (idx["GATE_REV"], "GATE_REV"),
                       (idx["GND"], "GND"), layer="F.Cu",
                       kind="R", lcsc="C25804"))
    # D_GREV 5V1 zener SOD-523: cathode = VBAT_CELL (Q_REV source pin 2
    # at qrev_x+0.95, qrev_y-1.1); anode = GATE_REV (Q_REV pin 1 rail).
    # Place D_GREV east of Q_REV on F.Cu at (qrev_x+2.5, qrev_y-1.1)
    # rot 0 so its pads run along the same y=qrev_y-1.1 line as Q_REV
    # pins 1/2.
    #   pad 1 (cathode, VBAT_CELL) west at (qrev_x+1.9, qrev_y-1.1)
    #   pad 2 (anode, GATE_REV) east at (qrev_x+3.1, qrev_y-1.1)
    # VBAT_CELL track: Q_REV pin 2 east edge (qrev_x+1.35, qrev_y-1.1)
    # -> D_GREV pad 1 west edge (qrev_x+1.6, qrev_y-1.1). Gap 0.25 mm;
    # connect with a 0.25 mm F.Cu stub at y=qrev_y-1.1. GATE_REV from
    # D_GREV pad 2 is ~7 mm east of R_GREV pad 1, but these connect
    # through Q_REV pin 1 body (all same GATE_REV net). Route via
    # F.Cu track: D_GREV pad 2 (qrev_x+3.1, qrev_y-1.1) west along
    # y=qrev_y-3.0 (north of Q_REV pin 1 north edge at qrev_y-1.85)
    # around Q_REV to R_GREV pad 1 (qrev_x-1.95, qrev_y-0.6) via short
    # dog-leg. However Q_REV pin 1 IS GATE_REV (same net), so instead
    # of routing around, the track can run west at y=qrev_y-1.1
    # passing over Q_REV pin 1 (same net, no short) and land on R_GREV
    # pin 1's south edge -- but pin 1 (south) is at qrev_y-0.6 and the
    # track y=qrev_y-1.1 misses it. Simplest: D_GREV pad 2 -> west track
    # at y=qrev_y-1.1 -> passes over Q_REV pin 1 (GATE_REV merge OK) ->
    # still needs to connect to R_GREV pad 1 at qrev_y-0.6. Route short
    # north stub at x=qrev_x-1.95 from y=qrev_y-1.1 up to y=qrev_y-0.6.
    # Net: D_GREV pad 2 -> straight west F.Cu (y=qrev_y-1.1) -> Q_REV
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                           (idx["VBAT_SW"], "VBAT_SW"), layer="F.Cu",
                           lcsc="C116170"))

    # SW_PWR SPDT slide (TH): pin1 -> VBAT (ON), pin2 -> VBAT_SW (COM),
    # pin3 -> NC_SW (OFF, floating)
    sw_x, sw_y = x0 + 33, y0 + 19.0
    out.append(fp_spdt("SW_PWR1", sw_x, sw_y, 0,
                       (idx["VBAT"], "VBAT"),        # pin 1 -> VBAT (ON)
                       (idx["VBAT_SW"], "VBAT_SW"),  # pin 2 -> COM
                       (idx["NC_SW"], "NC_SW")))     # pin 3 -> NC

    # NTC + divider (M-NTC-LOC: within 5 mm of J_BAT).
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    #    (VUSB<->GND at (147.5, 115.5)).
    #
    # MCU front pad coordinates (pin (mcu_x +/- 8.75, ...)):
    #   pin 1  VUSB       y = mcu_y - 7.62
    #   pin 2  GND        y = mcu_y - 5.08
    #   pin 3  +3V3       y = mcu_y - 2.54
    #   pin 11 ROW0       y = mcu_y + 0.00 (right column, VBAT ADC side)
    #   pin 15 BAT+ VBAT  (mcu_x, mcu_y + 6.5) (back-side pad exposed F.Cu)

    # C1/C2/C3/C4 all on B.Cu, placed at positions offset in y from the
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
    # --- Power chain: JST -> Q_REV -> F1 -> SW_PWR -> MCU BAT+ --------------
    # J_BAT JST-PH horizontal, pin 1 at (jbat_x-1.0, jbat_y-3.0) = (107, 116)
    # VBAT_CELL; pin 2 at (jbat_x+1.0, jbat_y-3.0) = (109, 116) GND.
    # VBAT_CELL F.Cu path at any y between 114 and 120 collides with JST
    # pad 2 (y=116), R_GREV pads (y=117.4, 118.4), Q_REV pins (y=117.9,
    # 117.9, 120.1), D_GREV pads (y=117.9), or R_GREV body. Solution:
    # carry VBAT_CELL on B.Cu from JST pad 1 via to Q_REV pin 2 via,
    # both same-net vias on their respective F.Cu pads. GND pour on
    # B.Cu carves around the VBAT_CELL 0.8-mm track by the default
    # 0.25 mm clearance.
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    # qrev_p2 y=117.9. But the north stub at x=qrev_x+0.95=116.95 from
    # y=121 to y=117.9 passes over Q_REV pin 3 F.Cu at (116, 120.1) --
    # x=116.95 vs 116 is 0.95 mm east of pin 3 centre; pin 3 extends
    # 115.6..116.4 in x, so 0.55 mm clear. F.Cu Q_REV pin 3 is VBAT_F,
    # B.Cu track VBAT_CELL different net but DIFFERENT LAYER -- no
    # short. OK.
    ew_y_b = jbat_y + 2.0   # B.Cu east-west at y=121
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    #   pin i LEFT  = (mcu_x-8.75, mcu_y + (i-4)*2.54) for i in 1..7
    #   pin i RIGHT = (mcu_x+8.75, mcu_y + (i-11)*2.54) for i in 8..14
    # Column pin -> key column mapping:
    #   pin 4=COL0, 5=COL1, 6=COL2, 7=COL3 (left column of MCU, south-to-north)
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
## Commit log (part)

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2026-04-21 keyboard
